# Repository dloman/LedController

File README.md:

LedController
=============

Controller board for led strips

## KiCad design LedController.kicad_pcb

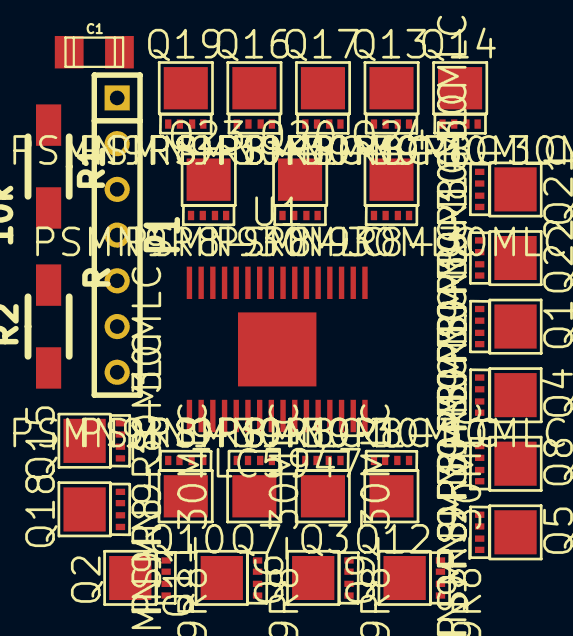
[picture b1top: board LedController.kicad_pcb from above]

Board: 2 copper layers, 29 parts (0 on the bottom side), 32 nets, no tracks yet.

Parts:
C1: 20n; c_1206
P1: CONN_7; SIL-7
Q1, Q2, Q3, Q4, Q5, Q6, Q7, Q8, Q9, Q10, Q11, Q12, Q13, Q14, Q15, Q16, Q17, Q18, Q19, Q20, Q21, Q22, Q23, Q24: PSMN9R8-30MLC
R1: 10k; Resistor_SMD1206_HandSoldering
R2: R; Resistor_SMD1206_HandSoldering
U1: TLC5947; tlc5947

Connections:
+5V: C1.1, P1.1, R1.1, U1.32
BLANK: P1.3, R1.2, U1.2
GND: C1.2, P1.2, Q1.D, Q2.D, Q3.D, Q4.D, Q5.D, Q6.D, Q7.D, Q8.D, Q9.D, Q10.D, Q11.D, Q12.D, Q13.S, Q14.S, Q15.S, Q16.S, Q17.S, Q18.S, Q19.S, Q20.S, Q21.S, Q22.S, Q23.S, Q24.S, U1.1
unnamed: Q1.G, U1.13
unnamed: Q2.G, U1.5
unnamed: Q3.G, U1.10
unnamed: Q4.G, U1.14
unnamed: Q5.G, U1.12
unnamed: Q6.G, U1.9
unnamed: Q7.G, U1.7
unnamed: Q8.G, U1.15
unnamed: Q9.G, U1.11
unnamed: Q10.G, U1.6
unnamed: Q11.G, U1.8
unnamed: Q12.G, U1.16
unnamed: Q13.G, U1.22
unnamed: Q14.G, U1.19
unnamed: Q15.G, U1.28
unnamed: Q16.G, U1.25
unnamed: Q17.G, U1.21
unnamed: Q18.G, U1.18
unnamed: Q19.G, U1.27
unnamed: Q20.G, U1.24
unnamed: Q21.G, U1.20
unnamed: Q22.G, U1.17
unnamed: Q23.G, U1.26
unnamed: Q24.G, U1.23
unnamed: R2.1, U1.31
SCLK: P1.4, U1.3
SIN: P1.5, U1.4
SOUT: P1.7, U1.29
XLAT: P1.6, U1.30

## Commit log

2014-06-04 Added intial schematic
2014-06-15 Added FET footprint and did inital board placement
2015-03-25 finished version 1.2
2015-04-13 updated schematic for new smaller more modular version
2015-04-18 added sparkfun lib so i dont have to do tssop16 footprint
2015-08-23 flipped logo
2015-09-13 changed headers to smaller nonreversible ones
2015-09-13 removed silkscreen for 5 pin header
